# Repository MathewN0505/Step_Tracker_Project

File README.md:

# Step_Tracker_Project
This project implements a system used to track a users steps.

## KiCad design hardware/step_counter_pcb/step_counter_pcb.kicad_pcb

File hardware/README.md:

# Hardware Design
This folder contains the files for the PCB for the step tracker

## Table of contents:

## Power Block
This block of the PCB contains the supply of power to the system. This consists of 3 main components:

1. A 3.7 Volt LiPo battery 
2. A TPS63031DS regulator for buck/boost conversion 
3. A push button to control on/off of system

The net labels are as follows:
- VBAT+ : the positive end of the LiPo Battery
- VBAT_SW: the voltage after going through the switch 
- 3V3: The regulated voltage

## Controller Block
This block of the PCB contains the main schematic for the controller (ESP32-C3-Mini-1). This connects the controller to all the peripherals of the PCB. The main layout is as follows:

1. Connection to the accelerometer
2. Connection to the LCD 
3. Connection to the EEPROM 
4. Connection to the Power Supply
5. Connection to the USB-C receptacle for programming/debugging 
6. Push button for resetting of the controller

The net labels are as follows:

- I2C_SDA: The Serial Data line for the accelerometer and EEPROM data
- I2C_SCL: The Serial Clock line for the accelerometer and EEPROM clock
- ACC_INT1: The accelerometer's step interrupt 
- LCD_SCK: The LCD serial clock
- LCD_MOSI: The LCD serial data
- LCD_CS: The LCD Chip Select
- LCD_A0: The LCD command/data selection
- LCD_RESET: The LCD reset 

## Accelerometer Block
This block of the PCB contains the accelerometer (LSM6DS3TR-C). It is connected to the controller block via I2C, and also has an interrupt pin for step detection. 

## Memory Block
This block of the PCB contains the EEPROM (AT24C04). It is connected to the controller block via I2C, and is used to store the step count. 

## Display Block
This block of the PCB contains the LCD (SSD1306B02). It is connected to the controller block via I2C, and is used to display the step count.

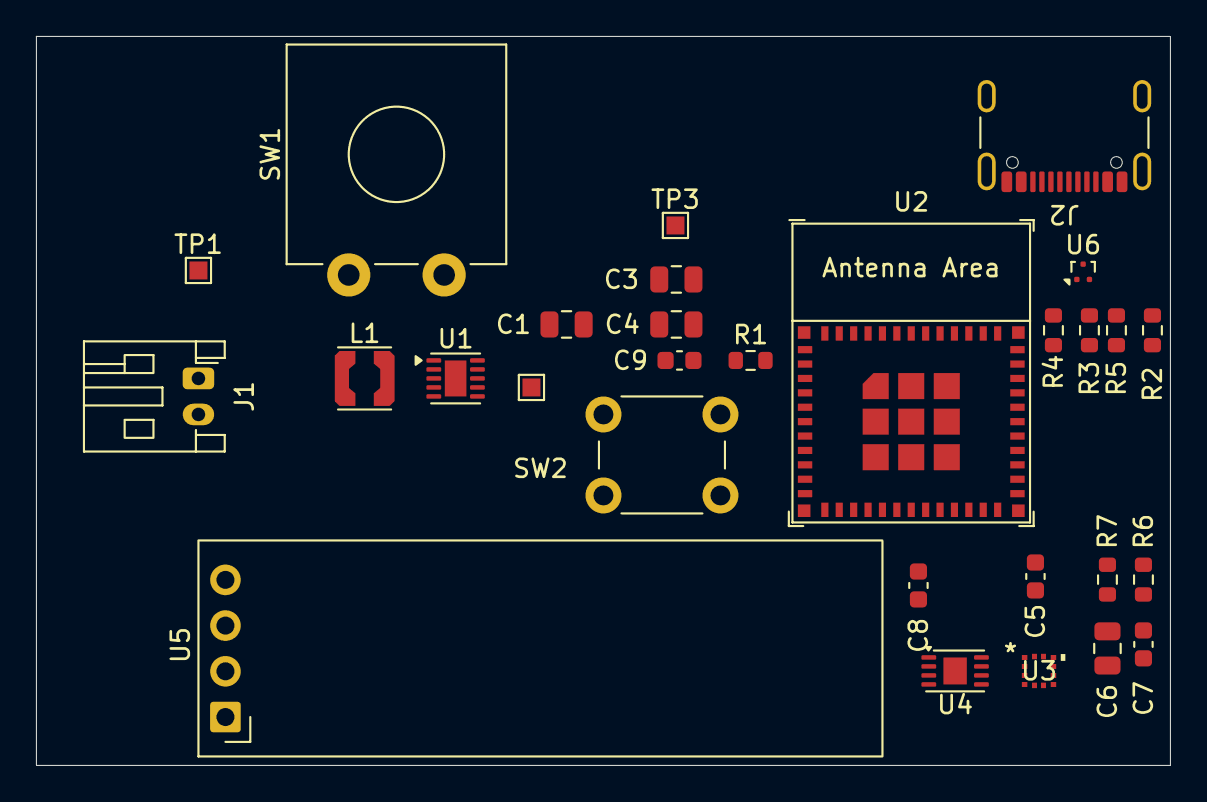
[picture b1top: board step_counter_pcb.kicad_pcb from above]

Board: 2 copper layers, 63.0 x 40.5 mm, 29 parts (0 on the bottom side), 16 nets, no tracks yet.

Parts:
C1, C3, C4, C6: 10 uF; C_0805_2012Metric
C5, C7, C8: 100 nF; C_0603_1608Metric
C9: 0.1 uF; C_0603_1608Metric
J1: LiPo_Battery; JST_PH_S2B-PH-K_1x02_P2.00mm_Horizontal
J2: USB_C_Receptacle_USB2.0_16P; USB_C_Receptacle_GCT_USB4105-xx-A_16P_TopMnt_Horizontal
L1: 1.5 uH; L_Coilcraft_LPS3010
R1: 10k; R_0603_1608Metric
R2, R3: 33; R_0603_1608Metric
R4, R5: 5.1 k; R_0603_1608Metric
R6, R7: 4.7 k; R_0603_1608Metric
SW1: SW_SPST; SW_CW_GPTS203211B
SW2: SW_Push; SW_PUSH_6mm
TP1: VBAT; TestPoint_Pad_1.0x1.0mm
TP2: VBAT_SW; TestPoint_Pad_1.0x1.0mm
TP3: TestPoint; TestPoint_Pad_1.0x1.0mm
U1: TPS63031DSK; WSON-10-1EP_2.5x2.5mm_P0.5mm_EP1.2x2mm
U2: ESP32-C3-MINI-1
U3: LIS2DUX12; LGA-12_2.0X2.0X0.74_LIS2DUX12_STM
U4: EEPROM; DFN-8-1EP_3x2mm_P0.5mm_EP1.3x1.5mm
U5: ER_OLEDM0.91_1x-I2C
U6: TPD2EUSB30; Texas_DRT-3

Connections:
/3V3: C3.1, C4.1, C5.2, C6.1, C7.1, C8.2, R1.1, R6.2, R7.1, TP3.1 (1_1), U1.1 (VOUT), U1.10 (FB), U2.3 (3V3), U3.2 (CS), U3.9 (VDD), U3.10 (VDD_IO), U4.8 (VCC), U5.2 (VCC)
/ACC_INT1: U2.6 (GPIO3/ADC1_CH3), U3.12 (INT1)
/I2C_SCL: R7.2, U2.19 (GPIO5/ADC2_CH0), U3.1 (SCL/SPC), U4.6 (SCL), U5.3 (SCL)
/I2C_SDA: R6.1, U2.18 (GPIO4/ADC1_CH4), U3.4 (SDA/SDI/SDO), U4.5 (SDA), U5.4 (SDA)
/VBAT+: J1.1, SW1.1 (A), TP1.1 (1_1)
/VBAT_SW: C1.1, C9.2, SW1.2 (B), TP2.1 (1_1), U1.5 (VIN), U1.6 (EN), U1.8 (VINA)
GND: C1.2, C3.2, C4.2, C5.1, C6.2, C7.2, C8.1, C9.1, J1.2, J2.A1 (GND), J2.A12 (GND), J2.B1 (GND), J2.B12 (GND), J2.SH (SHIELD), R4.2, R5.2, SW2.1, U1.3 (PGND), U1.7 (PS/SYNC), U1.9 (GND), U1.11 (PGND), U2.1 (GND), U2.2 (GND), U2.11 (GND), U2.14 (GND), U2.36 (GND), U2.37 (GND), U2.38 (GND), U2.39 (GND), U2.40 (GND), U2.41 (GND), U2.42 (GND), U2.43 (GND), U2.44 (GND), U2.45 (GND), U2.46 (GND), U2.47 (GND), U2.48 (GND), U2.49 (GND), U2.50 (GND), U2.51 (GND), U2.52 (GND), U2.53 (GND), U3.3 (SDO/SA0), U3.6 (GND), U3.7 (RES), U3.8 (GND), U4.1 (A0), U4.2 (A1), U4.3 (A2), U4.4 (GND), U4.7 (WP), U4.9 (GND), U5.1 (GND), U6.3 (GND)
unnamed: J2.A5 (CC1), R5.1
unnamed: J2.B5 (CC2), R4.1
unnamed: L1.2, U1.4 (L1)
unnamed: L1.1, U1.2 (L2)
unnamed: R1.2, SW2.2, U2.8 (EN/CHIP_PU)
unnamed: R3.2, U2.26 (GPIO18/USB_D-)
unnamed: R2.2, U2.27 (GPIO19/USB_D+)
unnamed: J2.A6 (D+), J2.B6 (D+), R2.1, U6.1 (D+)
unnamed: J2.A7 (D-), J2.B7 (D-), R3.1, U6.2 (D-)
